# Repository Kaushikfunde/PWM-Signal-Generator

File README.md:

# PWM Signal Generator & Analyzer

**A dual-range NE555 PWM generator paired with an ESP32 frequency counter, built on a custom single-sided KiCad PCB.**

**Case study:** [PWM Signal Generator & Analyzer](https://kaushikfunde.vercel.app/#/work/pwm-analyzer)

## Overview

This project combines a classic 555-timer oscillator with a modern microcontroller measurement stage. The NE555 runs as an astable multivibrator and produces a 5 V square wave. An SPDT switch selects between two timing capacitors, and a 10 kΩ potentiometer tunes the frequency within the selected range. The ESP32 counts the incoming pulses over a one-second window and displays the frequency and range status on a 128×64 OLED.

The board was designed in KiCad, fabricated as a single-sided PCB, and assembled by hand as a third-semester course project.

**Status:** Prototype — the PCB has been fabricated and partially assembled; final electrical validation is pending.

## Features

- Dual-range NE555 astable oscillator: 150 nF and 1 µF timing capacitors
- Continuous frequency tuning with an external 10 kΩ potentiometer
- ESP32 hardware-interrupt frequency counter with a 1-second gate
- 128×64 I²C OLED readout using the U8g2 library
- 115200 baud serial telemetry for debugging
- Screw-terminal connections for the generator output and external controls
- Custom single-sided PCB designed and routed in KiCad

## At a glance

| | |
|---|---|
| **Generator** | NE555P astable multivibrator, 5 V |
| **Ranges** | 150 nF / 1 µF timing capacitors |
| **Controller** | ESP32-WROOM-32 DevKitC |
| **Display** | 128×64 I²C OLED (SH1106) |
| **Input** | GPIO34, rising-edge interrupt |
| **PCB** | Single-sided, KiCad 10, hand-etched |
| **Firmware** | Arduino C++ |
| **License** | MIT |

## System overview

```text
        ┌──────────────────┐   5 V square wave   ┌──────────────────┐
        │  NE555 astable   │ ──────────────────► │  conditioning /  │
        │  range + tuning  │                     │  GPIO34 input    │
        └────────┬─────────┘                     └────────┬─────────┘
                 │                                        │
          C2 / C3 range                            ESP32-WROOM-32
          RV1 tuning                                     │
                                                 I2C OLED 128×64
```

The NE555 timing network is formed by R1, R4, RV1, and the selected capacitor. SW2 selects C2 (150 nF) for the higher range or C3 (1 µF) for the lower range. The generator output is available at the J1 screw terminal and is also conditioned before reaching the ESP32 input.

The firmware uses an interrupt on GPIO34 to count rising edges. Every second it copies the pulse count safely with interrupts disabled, computes the frequency, reads the range-sense pin, and refreshes the OLED.

## Hardware

| Ref | Part | Value / notes |
|---|---|---|
| U1 | ESP32 DevKitC | ESP32-WROOM-32 |
| U2 | NE555P | Astable oscillator |
| U3 | OLED module | 128×64, I²C, SH1106-compatible |
| R1 | Resistor | 1 kΩ |
| R2 | Resistor | 100 Ω, output series |
| R3 | Resistor | 330 Ω, series to GPIO34 |
| R4 | Resistor | 1 kΩ |
| R5 | Resistor | 10 kΩ, input load |
| RV1 | Potentiometer | 10 kΩ, external |
| C1 | Capacitor | 10 nF |
| C2 | Capacitor | 150 nF |
| C3 | Capacitor | 1 µF, 63 V |
| C4 | Capacitor | 100 µF, 25 V |
| C5 | Capacitor | 10 nF |
| SW2 | Switch | SPDT range selector |
| J1 | Terminal block | 2-pin generator output |

### Pinout

| ESP32 pin | Connection | Purpose |
|---|---|---|
| GPIO34 | Conditioned NE555 output | Pulse input (interrupt) |
| GPIO27 | Range-sense line | Range select (see note below) |
| GPIO21 | OLED SDA | I²C data |
| GPIO22 | OLED SCL | I²C clock |
| 5V / GND | NE555 VCC / GND | Supply and common ground |

## Firmware

The sketch is at [`firmware/minorprojectv1.0/minorprojectv1.0.ino`](firmware/minorprojectv1.0/minorprojectv1.0.ino).

### Build and upload

1. Install the **ESP32 board package** in Arduino IDE.
2. Install the **U8g2** library via Library Manager.
3. Open `firmware/minorprojectv1.0/minorprojectv1.0.ino`.
4. Select **ESP32 Dev Module** and the correct serial port.
5. Upload, then open the Serial Monitor at **115200 baud**.

The ESP32 is powered over USB, while the NE555 stage is powered from an external 5 V supply. Both sections share a common ground.

### Current behavior

- Counts rising edges on GPIO34 for one second.
- Prints `Frequency: <value> Hz` to the serial monitor.
- Displays the frequency and the state of GPIO27 on the OLED.
- The range pin uses `INPUT_PULLUP`: HIGH reports `A (1 uF)`, LOW reports `B (150 nF)`.

## Design files

Open [`hardware/MinorProject.kicad_pro`](hardware/MinorProject.kicad_pro) with **KiCad 10** or newer.

- [`hardware/MinorProject.kicad_sch`](hardware/MinorProject.kicad_sch) — schematic
- [`hardware/MinorProject.kicad_pcb`](hardware/MinorProject.kicad_pcb) — PCB layout
- [`hardware/MinorProject-Schematic.pdf`](hardware/MinorProject-Schematic.pdf) — exported schematic
- [`hardware/fabrication/`](hardware/fabrication/) — copper, mask, paste, silkscreen, and edge-cut plots
- [`hardware/DPDTswitch.pretty/`](hardware/DPDTswitch.pretty/) — custom switch footprint

## Build photos

| Breadboard prototype | Fabricated PCB |
| --- | --- |
|  |  |

| Range switch detail | KiCad PCB render |
| --- | --- |
|  |  |

## Repository layout

```text
.
├── firmware/
│   └── minorprojectv1.0/
│       └── minorprojectv1.0.ino
├── hardware/
│   ├── fabrication/
│   ├── DPDTswitch.pretty/
│   ├── MinorProject.kicad_pro
│   ├── MinorProject.kicad_sch
│   ├── MinorProject.kicad_pcb
│   ├── MinorProject-Schematic.pdf
│   └── fp-lib-table
├── images/
├── LICENSE
└── README.md
```

## Design notes and next revision

These are the known gaps in the current prototype, documented for the next board revision:

- **Input protection.** The PCB revision here uses R2 (100 Ω), R3 (330 Ω), and R5 (10 kΩ). This limits current but does not divide the 5 V output down to 3.3 V at GPIO34. Add the 6.8 kΩ / 10 kΩ divider specified in the project report (≈2.97 V) or a proper level shifter before connecting the ESP32.
- **Range sense.** GPIO27 is reserved for range detection, but it is not routed on the current PCB. The firmware's internal pull-up therefore reports Range A. The next revision should wire the second pole of the selector switch to GPIO27.
- **Measurement.** The current firmware measures frequency only. Duty-cycle and period measurement via CHANGE-edge interrupts are the next firmware step.
- **Validation.** Complete assembly and run the test plan: power-on, range switching, frequency tuning, divider voltage, no-signal handling, external output, and sustained stability.

## Author

Built by **Kaushik Funde** — electronics engineering student at G. H. Raisoni College of Engineering, Nagpur.

[Portfolio](https://kaushikfunde.vercel.app/) · [GitHub](https://github.com/Kaushikfunde) · [LinkedIn](https://www.linkedin.com/in/kaushik-funde-239925373/)

## License

Released under the [MIT License](LICENSE).

Third-party components — including the Arduino ESP32 core, U8g2, and KiCad libraries — remain under their own licenses.

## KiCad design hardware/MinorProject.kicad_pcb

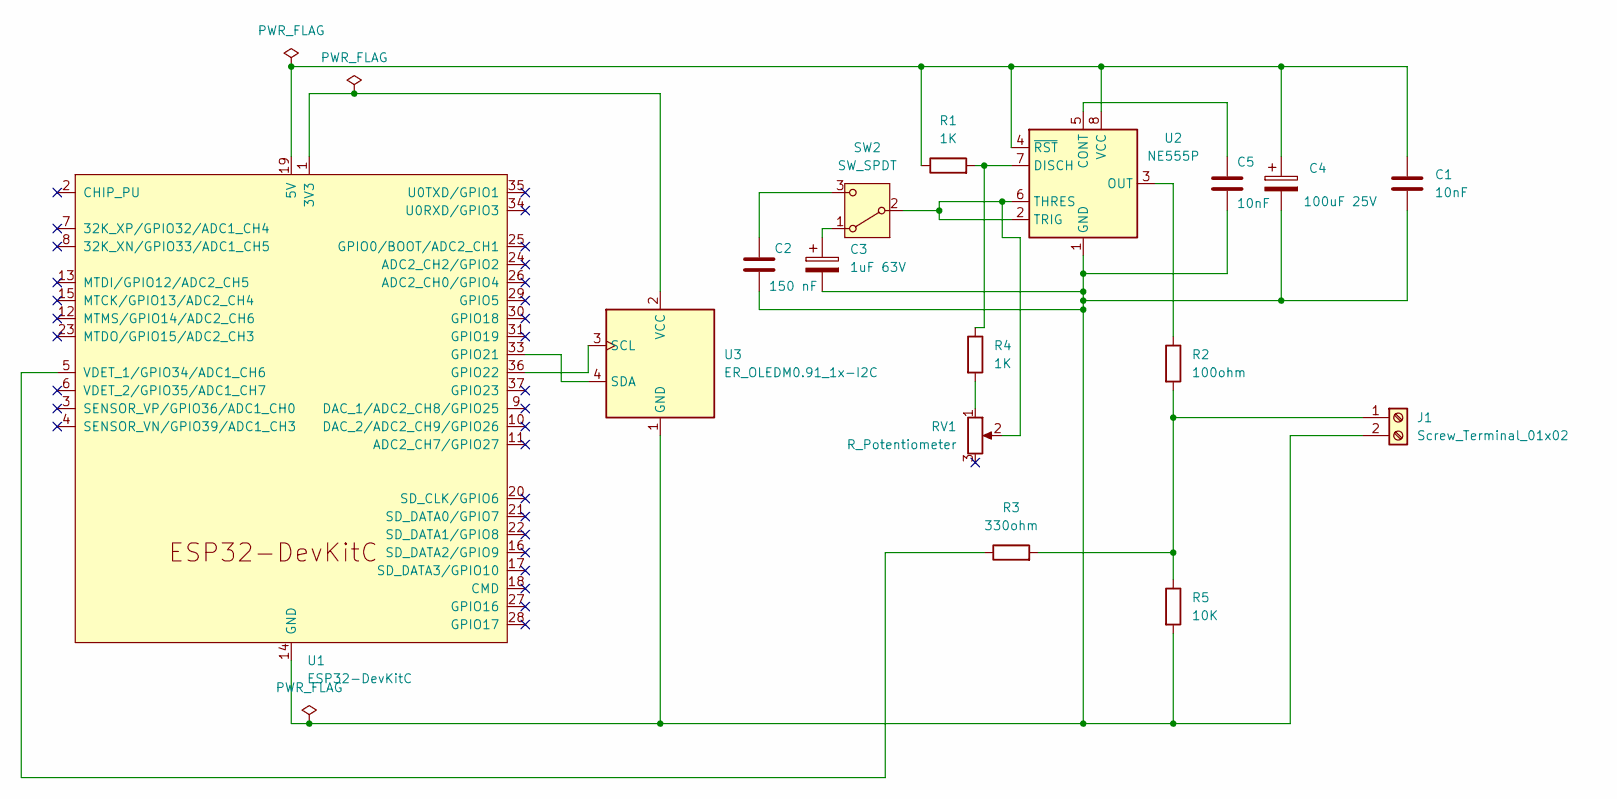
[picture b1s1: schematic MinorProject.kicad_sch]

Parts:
C1, C5: 10nF; CP_Radial_Tantal_D5.0mm_P2.50mm
C2: 150 nF; CP_Radial_Tantal_D5.0mm_P2.50mm
C3: 1uF 63V; CP_Radial_D4.0mm_P1.50mm
C4: 100uF 25V; CP_Radial_D4.0mm_P2.00mm
J1: Screw_Terminal_01x02; TerminalBlock_MetzConnect_Type011_RT05502HBLC_1x02_P5.00mm_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
R1, R4: 1K; R_Axial_DIN0309_L9.0mm_D3.2mm_P12.70mm_Horizontal
R2: 100ohm; R_Axial_DIN0309_L9.0mm_D3.2mm_P12.70mm_Horizontal
R3: 330ohm; R_Axial_DIN0309_L9.0mm_D3.2mm_P12.70mm_Horizontal
R5: 10K; R_Axial_DIN0309_L9.0mm_D3.2mm_P12.70mm_Horizontal
RV1: R_Potentiometer; Potentiometer_Vishay_T93YA_Vertical
SW2: SW_SPDT; Untitled
U1: ESP32-DevKitC
U2: NE555P; DIP-8_W7.62mm
U3: ER_OLEDM0.91_1x-I2C

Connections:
unnamed: J1.1, R2.2, R3.2, R5.1
unnamed: C1.2, C2.2, C3.2, C4.2, C5.2, J1.2, R5.2, U1.14 (GND), U1.32 (GND), U1.38 (GND), U2.1 (GND), U3.1 (GND)
unnamed 2: RV1.2, SW2.2 (B), U2.2 (TRIG), U2.6 (THRES); also elsewhere on the board
unnamed 3: R4.2, RV1.1; also elsewhere on the board
unnamed: C3.1, SW2.1 (A)
unnamed: C2.1, SW2.3 (C)
unnamed: U1.1 (3V3), U3.2 (VCC)
unnamed: C1.1, C4.1, R1.1, U1.19 (5V), U2.4 (~RST), U2.8 (VCC)
unnamed: U1.33 (GPIO21), U3.4 (SDA)
unnamed: U1.36 (GPIO22), U3.3 (SCL)
unnamed: R3.1, U1.5 (VDET_1/GPIO34/ADC1_CH6)
unnamed: C5.1, U2.5 (CONT)
unnamed: R1.2, R4.1, U2.7 (DISCH)
unnamed: R2.1, U2.3 (OUT)

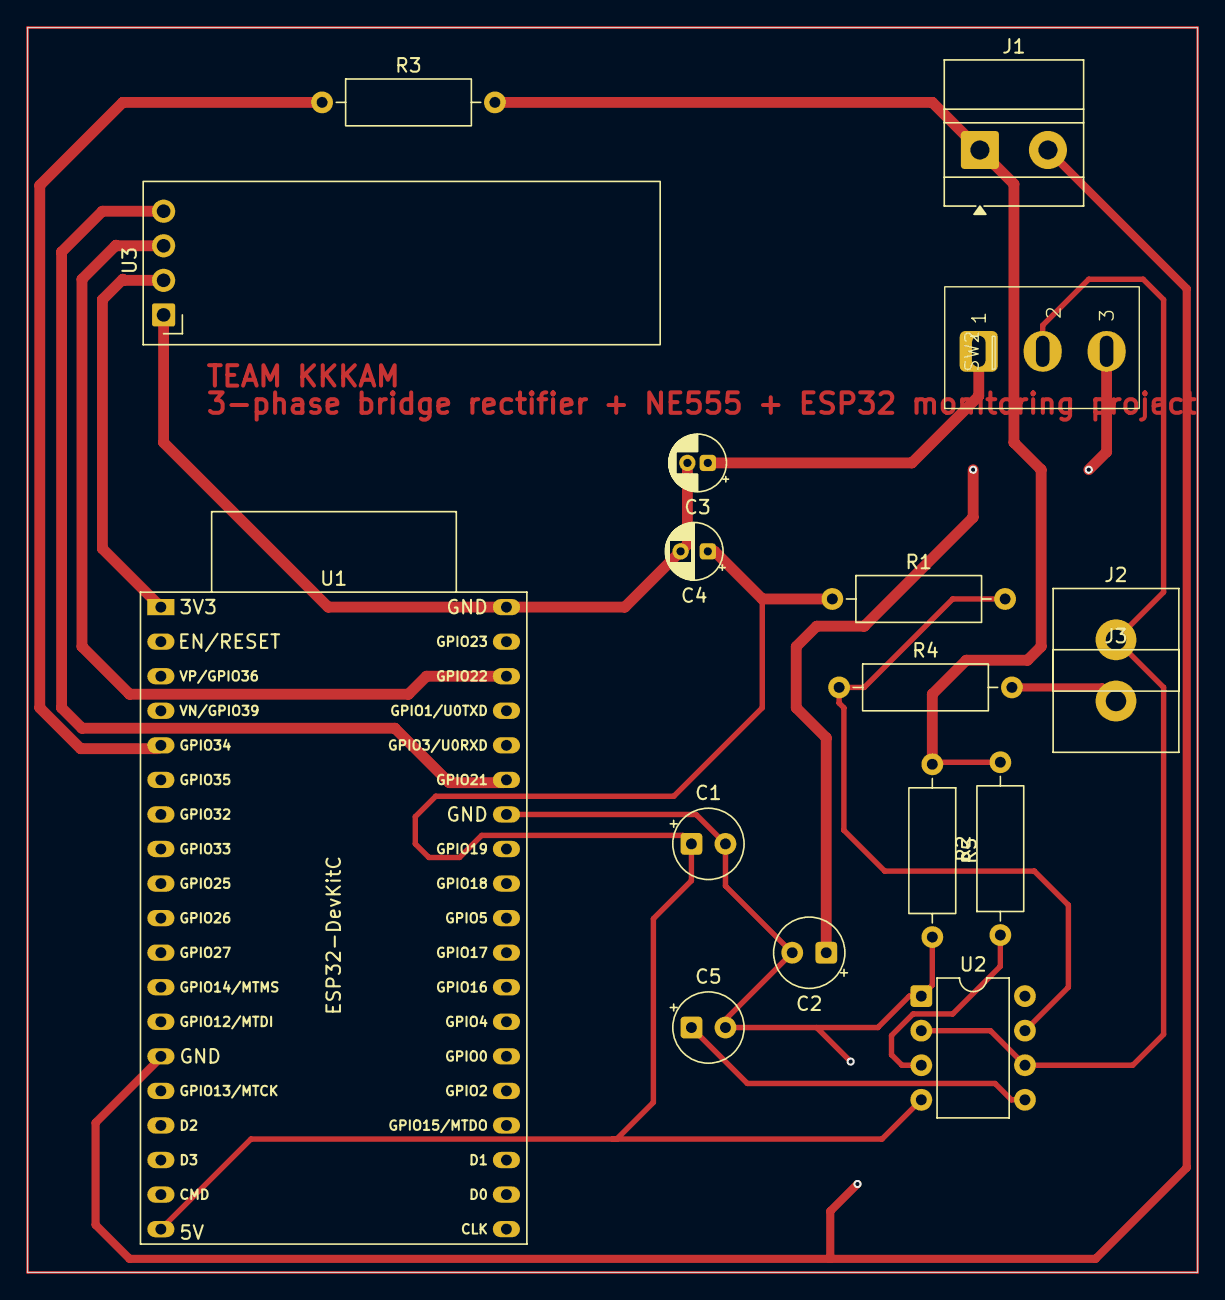
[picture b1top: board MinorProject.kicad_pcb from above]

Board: 2 copper layers, 86.0 x 91.5 mm, 17 parts (0 on the bottom side), 14 nets.

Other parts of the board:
J2, J3: Screw_Terminal_01x01; TerminalBlock_MetzConnect_360271_1x01_Horizontal_ScrewM3.0_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

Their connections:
unnamed 2: J2.1 (Pin_1_1); also elsewhere on the board
unnamed 3: J3.1 (Pin_1_1); also elsewhere on the board
